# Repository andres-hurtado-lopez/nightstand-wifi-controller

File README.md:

# nightstand-wifi-controller
A WIFI controller for my nightstand lamp

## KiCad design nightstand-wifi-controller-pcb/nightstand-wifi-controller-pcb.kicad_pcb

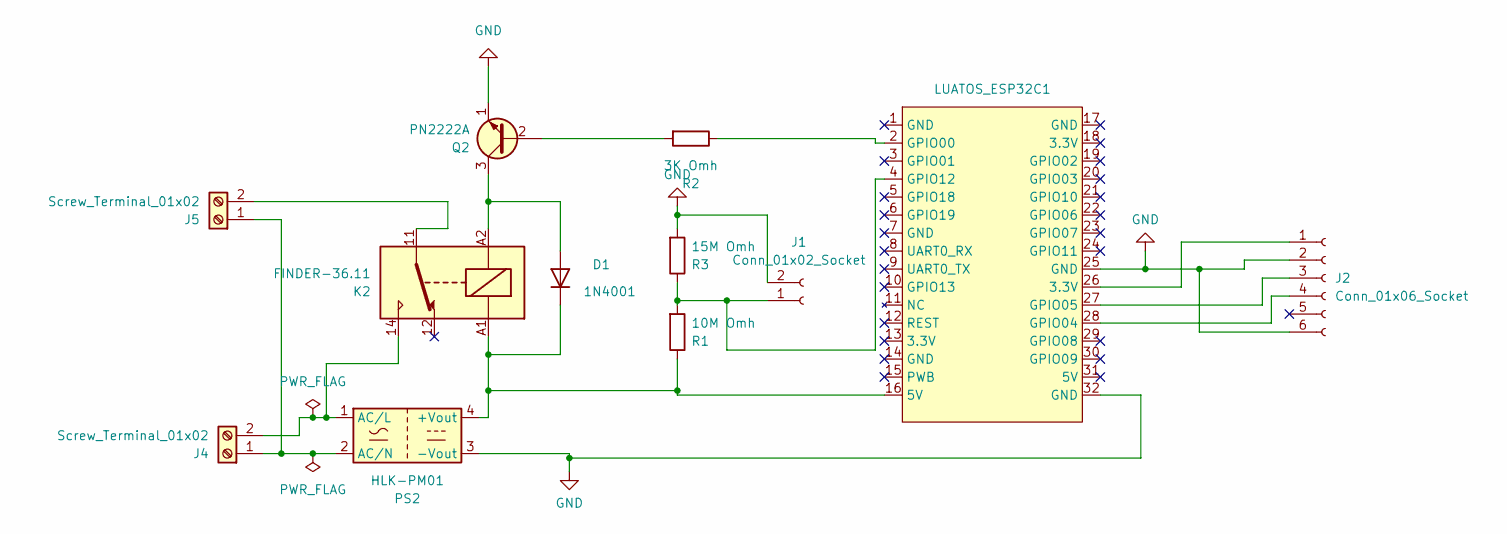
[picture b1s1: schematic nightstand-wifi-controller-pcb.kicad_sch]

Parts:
D1: 1N4001; D_DO-41_SOD81_P10.16mm_Horizontal
J1: Conn_01x02_Socket; PinSocket_1x02_P2.54mm_Vertical
J2: Conn_01x06_Socket; PinSocket_1x06_P2.54mm_Vertical
J4, J5: Screw_Terminal_01x02; TerminalBlock_Altech_AK300-2_P5.00mm
K2: FINDER-36.11; Relay_SPDT_Finder_36.11
LUATOS_ESP32C1: luatos_esp32c3
PS2: HLK-PM01; Converter_ACDC_HiLink_HLK-PMxx
Q2: PN2222A; TO-92_HandSolder
R1: 10M Omh; R_Axial_DIN0207_L6.3mm_D2.5mm_P10.16mm_Horizontal
R2: 3K Omh; R_Axial_DIN0207_L6.3mm_D2.5mm_P10.16mm_Horizontal
R3: 15M Omh; R_Axial_DIN0207_L6.3mm_D2.5mm_P10.16mm_Horizontal

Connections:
GND: J1.2, J2.2, J2.6, LUATOS_ESP32C1.25 (GND), LUATOS_ESP32C1.32 (GND), PS2.3 (-Vout), Q2.1 (E), R3.2
unnamed: D1.2 (A), K2.A2, Q2.3 (C)
unnamed: D1.1 (K), K2.A1, LUATOS_ESP32C1.16 (5V), PS2.4 (+Vout), R1.1
unnamed: J1.1, LUATOS_ESP32C1.4 (GPIO12), R1.2, R3.1
unnamed: J2.1, LUATOS_ESP32C1.26 (3.3V)
unnamed: J2.3, LUATOS_ESP32C1.27 (GPIO05)
unnamed: J2.4, LUATOS_ESP32C1.28 (GPIO04)
unnamed: J4.1, J5.1, PS2.2 (AC/N)
unnamed: J4.2, K2.14, PS2.1 (AC/L)
unnamed: J5.2, K2.11
unnamed: LUATOS_ESP32C1.2 (GPIO00), R2.1
unnamed: Q2.2 (B), R2.2

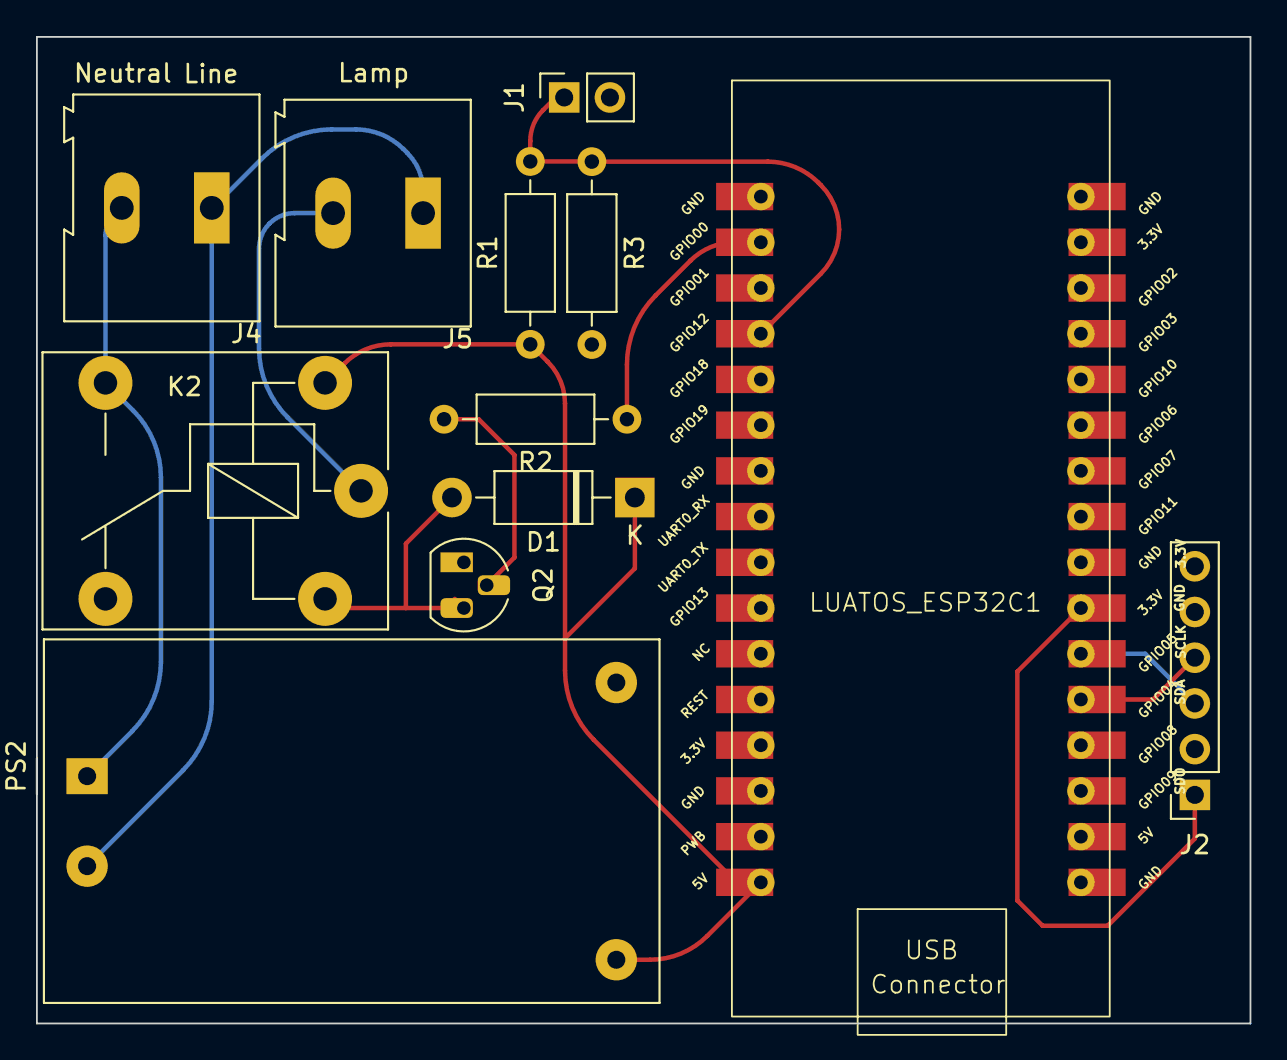
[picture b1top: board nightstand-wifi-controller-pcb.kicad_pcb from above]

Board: 2 copper layers, 67.4 x 54.8 mm, 12 parts (0 on the bottom side), 12 nets.

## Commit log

2023-12-28 First approach to create webserver. Pending to define connection to wifi
2023-12-31 Changed WIFI connection strategy to infrastructure client with DHCP. HTML menu implemented
2024-01-02 Added GIO task control. Led indicator for sucessful WIFI connection
2024-01-03 -Datasheets added -Attempt for sensor BMP280 support failed
2024-01-05 Read sensor data fixed on hardware and software.
    Temperature read first approach
2024-01-05 log removed
2024-01-05 Temperature capture achieved. Pressure capture still pending to decode reading
2024-01-06 Sensor datasheet
2024-01-06 PCB circuit design. Schematic
2024-01-07 First Approach to a PCB design
2024-01-07 Missing schematic changes
2024-01-07 PCB design completeed and JLCPCB Design rules set up
2024-01-07 Header pin sizes fixed from 1.27mm to 2.54mm
2024-01-08 GND fill fixed and Silkscreen of temperature sensor
2024-01-10 Fix on earth for mcu module
2024-01-20 Snubber diod added to relay coil and temp sensor socket location fixed
